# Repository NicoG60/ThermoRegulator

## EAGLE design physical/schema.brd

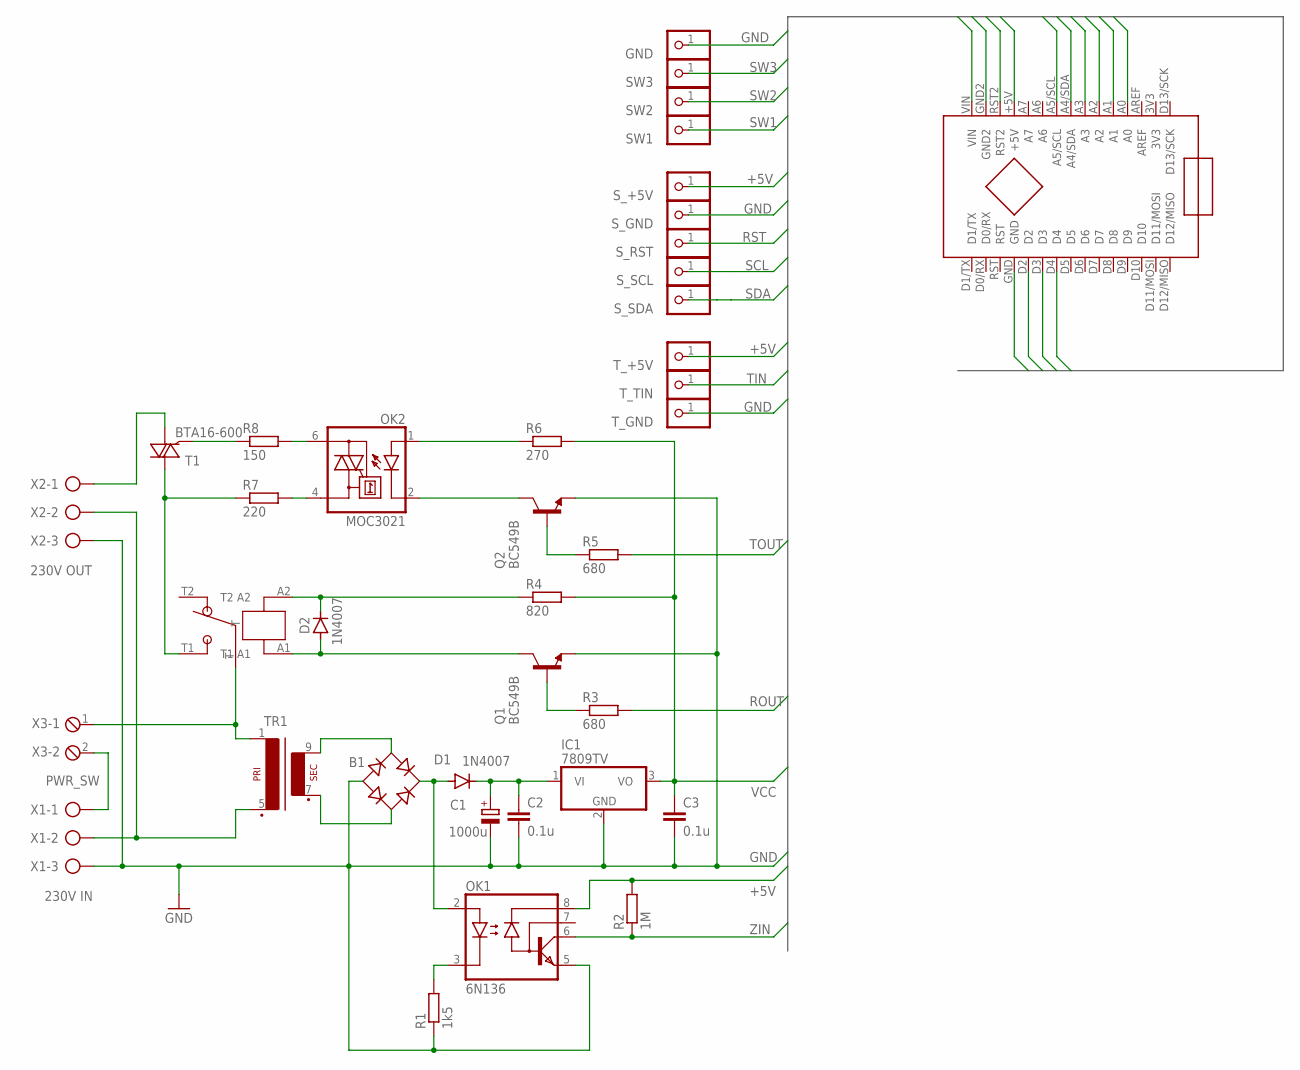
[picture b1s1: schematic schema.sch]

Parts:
B1: B-DIL
C1: 1000u; E5-8,5
C2, C3: 0.1u; C050-024X044
D1, D2: 1N4007; DO35-7
GND: PINHD-1X1; 1X01
IC1: 7809TV; TO220V
OK1: 6N136; DIL08
OK2: MOC3021; DIL06; MPN MOC3021
Q1, Q2: BC549B; TO92-EBC
R1: 1k5; 0204V
R2: 1M; 0204/5
R3, R5: 680; 0204/7
R4: 820; 0204/7
R6: 270; 0204/7
R7: 220; 0204/7
R8: 150; 0204/7
SW1, SW2, SW3: PINHD-1X1; 1X01
S_+5V: PINHD-1X1; 1X01
S_GND: PINHD-1X1; 1X01
S_RST: PINHD-1X1; 1X01
S_SCL: PINHD-1X1; 1X01
S_SDA: PINHD-1X1; 1X01
T1: BTA16-600; TO220BV
TR1: EI30-1
T_+5V: PINHD-1X1; 1X01
T_GND: PINHD-1X1; 1X01
T_TIN: PINHD-1X1; 1X01
U$1: FINDER_31.21.X; FINDER_32.21.X
U$2: ARDUINO_NANO
X1: 230V IN; AK500/3
X2: 230V OUT; AK500/3
X3: PWR_SW; 2POL254

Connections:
+5V: OK1.8 (VCC), R2.2, S_+5V.1, T_+5V.1, U$2.+5V
GND: B1.-, C1.-, C2.2, C3.2, GND.1, IC1.2 (GND), OK1.5 (GND), Q1.E, Q2.E, R1.1, S_GND.1, T_GND.1, U$2.GND, U$2.GND2, X1.3, X2.3
unnamed: X1.1, X3.2
unnamed: TR1.1, U$1.T, X3.1
unnamed: TR1.5 (P2), X1.2, X2.2
unnamed: OK1.3 (C), R1.2
unnamed: B1.AC1, TR1.9 (S4)
unnamed: B1.AC2, TR1.7 (S3)
unnamed: B1.+, D1.A, OK1.2 (A)
unnamed: C1.+, C2.1, D1.C, IC1.1 (VI)
unnamed: R7.1, T1.T2 (A2), U$1.T1
unnamed: T1.T1 (A1), X2.1
unnamed: D2.A, Q1.C, U$1.A1
unnamed: D2.C, R4.1, U$1.A2
unnamed: R8.1, T1.G
unnamed: OK2.6 (A2), R8.2
unnamed: OK2.4 (A1), R7.2
unnamed: Q1.B, R3.1
unnamed: Q2.B, R5.1
unnamed: OK2.2 (C), Q2.C
unnamed: OK2.1 (A), R6.1
ROUT: R3.2, U$2.A1
RST: S_RST.1, U$2.RST2
SCL: S_SCL.1, U$2.A5/SCL
SDA: S_SDA.1, U$2.A4/SDA
SW1: SW1.1, U$2.D2
SW2: SW2.1, U$2.D3
SW3: SW3.1, U$2.D4
TIN: T_TIN.1, U$2.A2
TOUT: R5.2, U$2.A0
VCC: C3.1, IC1.3 (VO), R4.2, R6.2, U$2.VIN
ZIN: OK1.6 (VO), R2.1, U$2.A3

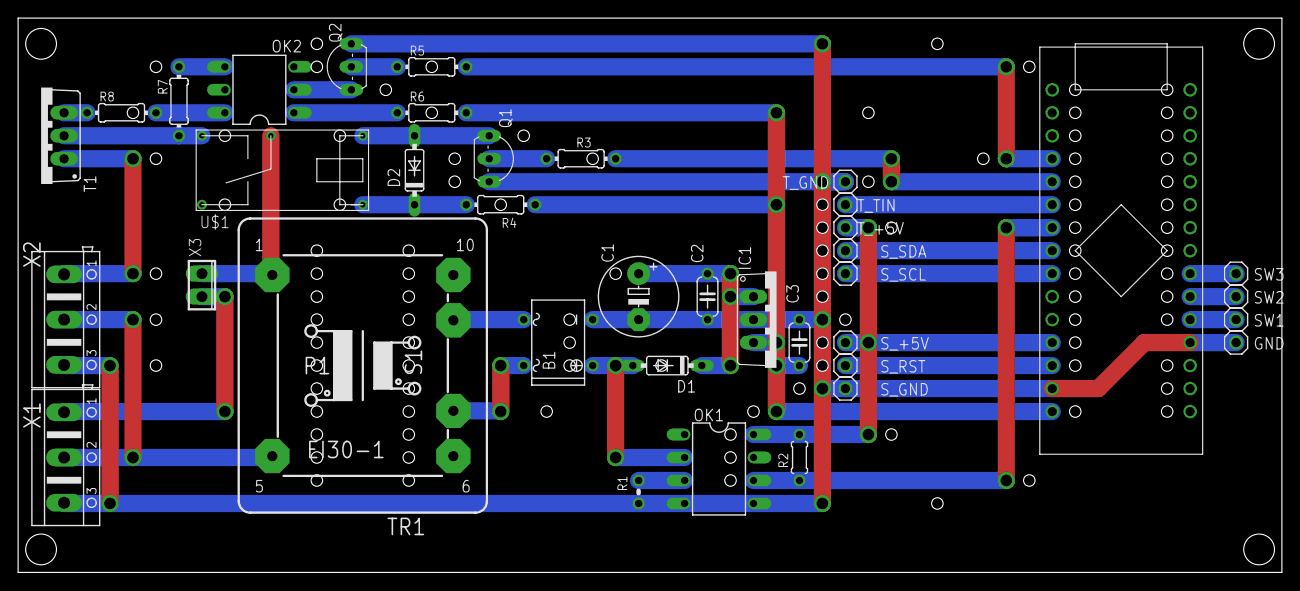
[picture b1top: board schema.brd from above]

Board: 2 copper layers, 139.7 x 61.3 mm, 38 parts (0 on the bottom side), 32 nets.

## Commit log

2020-12-17 content
2020-12-17 gitignore
2020-12-17 fix display issue
2020-12-17 fix flicker
